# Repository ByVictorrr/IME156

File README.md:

# IME156 - Basic Electronics Manufacturing.

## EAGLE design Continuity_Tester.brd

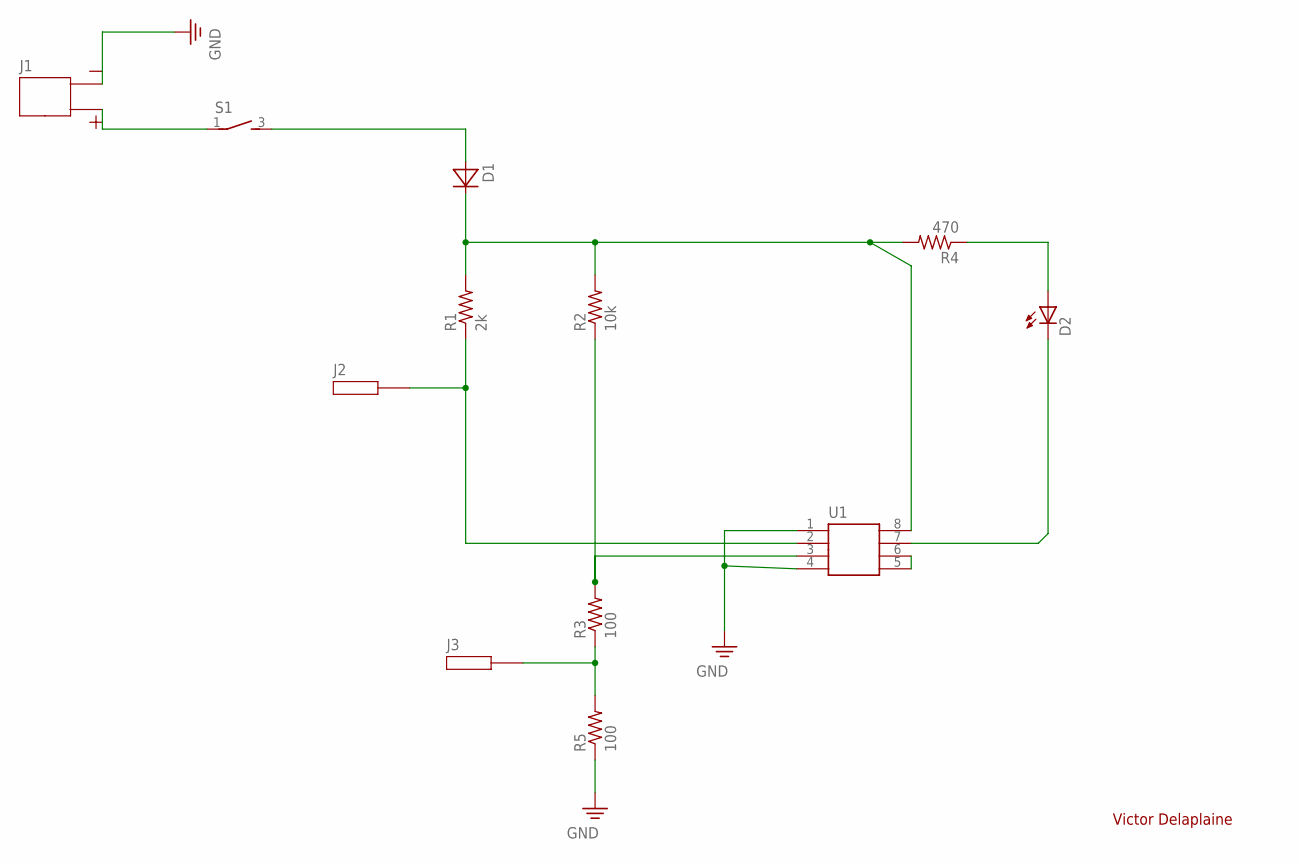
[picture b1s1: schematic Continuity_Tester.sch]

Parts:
D1: DIODE; DIODE-FOOT
D2: LED; LED-FOOT
J1: POWER; POWER-FOOT
J2, J3: ALLIGATORCLIP; ALLIGATORCLIP-FOOT
R1: 2k; RES-FOOT
R2: 10k; RES-FOOT
R3, R5: 100; RES-FOOT
R4: 470; RES-FOOT
S1: SWITCH; SWITCH-FOOT
U1: LM311M; LM311M-FOOT

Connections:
unnamed: J1.2, S1.1
unnamed: D1.A, S1.3
unnamed: D1.C, R1.2, R2.2, R4.2, U1.8
unnamed: J2.1, R1.1, U1.2
unnamed: J3.1, R3.1, R5.2
unnamed: D2.A, R4.1
unnamed: D2.C, U1.7
unnamed: U1.5, U1.6
unnamed: R2.1, R3.2, U1.3
PE: J1.1, R5.1, U1.1, U1.4

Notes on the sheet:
Victor Delaplaine

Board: 2 copper layers, 12 parts (0 on the bottom side), 10 nets, no tracks yet.

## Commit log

2019-02-20 autoadd
